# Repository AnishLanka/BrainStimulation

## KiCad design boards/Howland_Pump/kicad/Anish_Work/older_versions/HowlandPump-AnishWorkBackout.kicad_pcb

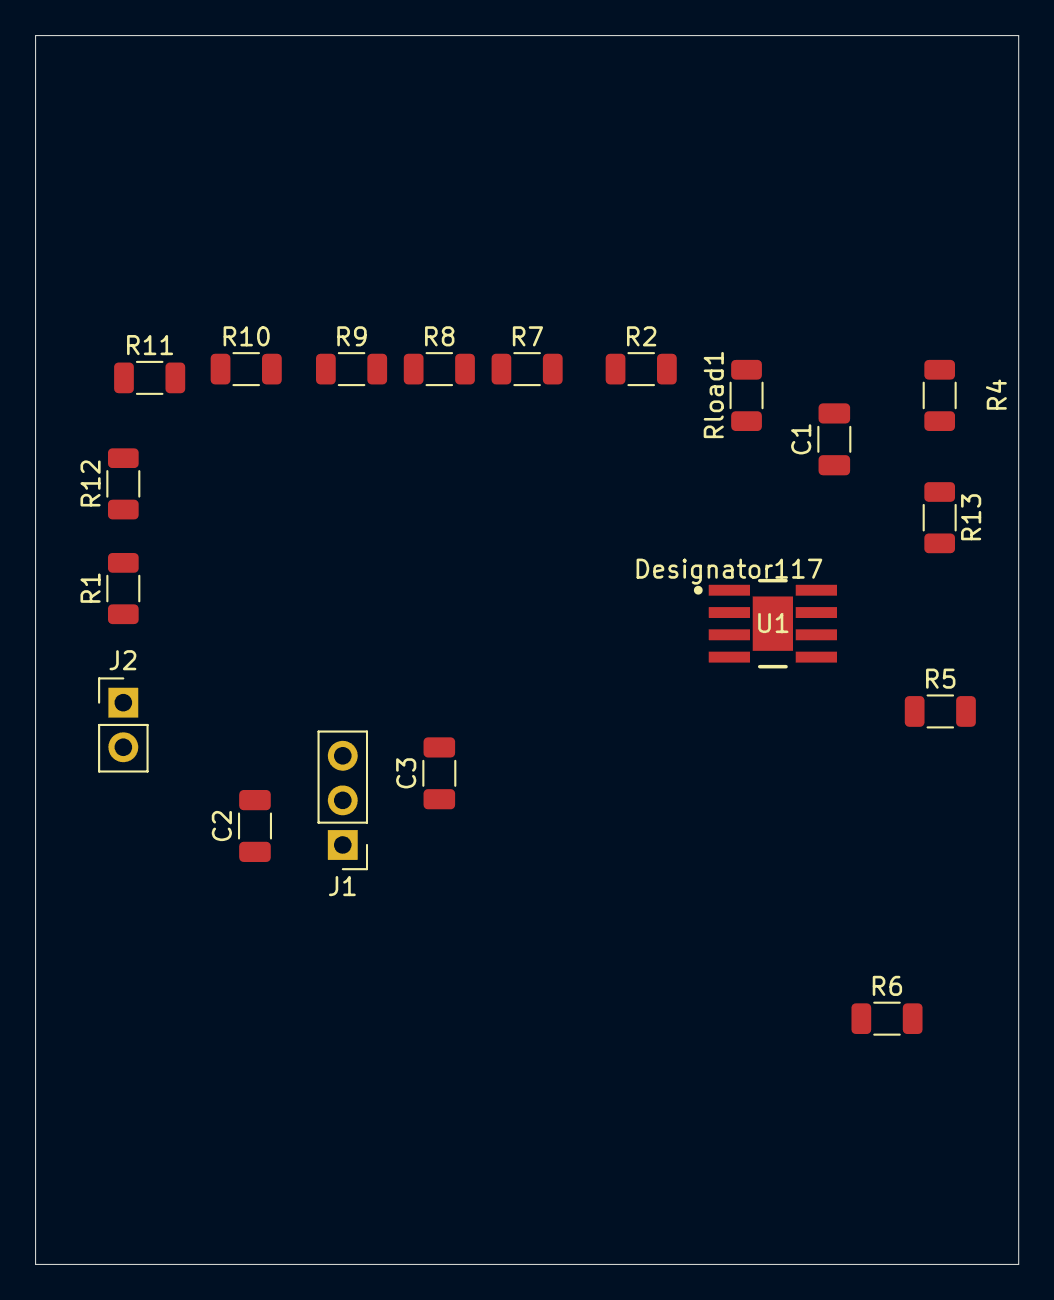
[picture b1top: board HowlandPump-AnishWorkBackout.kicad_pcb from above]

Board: 2 copper layers, 56.0 x 70.0 mm, 19 parts (0 on the bottom side), 16 nets, no tracks yet.

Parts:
C1: 30pF; C_1206_3216Metric
C2, C3: 100nF; C_1206_3216Metric
J1: Conn_01x03; PinHeader_1x03_P2.54mm_Vertical
J2: Conn_01x02; PinHeader_1x02_P2.54mm_Vertical
R1, R5, R6: 100K; R_1206_3216Metric
R2, R7, R8, R9, R10: 9.1K; R_1206_3216Metric
R4: 200; R_1206_3216Metric
R11: 20K; R_1206_3216Metric
R12: 30K; R_1206_3216Metric
R13: 300; R_1206_3216Metric
Rload1: 2K; R_1206_3216Metric
U1: OPA462IDDA; DDA0008J-IPC_A

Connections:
+40: C2.1, J1.1, U1.7 (V+)
-40: C3.2, J1.3, U1.4 (V-), U1.9 (PowerPAD)
GND: C1.2, C2.2, C3.1, J1.2, J2.2, R6.1, Rload1.1, U1.1 (E_D_Com)
unnamed: J2.1, R1.1
unnamed: R2.1, R7.2
unnamed: R2.2, R4.1, Rload1.2
unnamed: R7.1, R8.2
unnamed: R8.1, R9.2
unnamed: R10.1, R11.2
unnamed: R9.1, R10.2
unnamed: R11.1, R12.2
unnamed: R4.2, R13.1
unnamed: R1.2, R12.1, U1.3 (+IN)
unnamed: R5.1, R6.2, U1.2 (-IN)
unnamed: C1.1, U1.8 (E_D)
unnamed: R5.2, R13.2, U1.6 (OUT)

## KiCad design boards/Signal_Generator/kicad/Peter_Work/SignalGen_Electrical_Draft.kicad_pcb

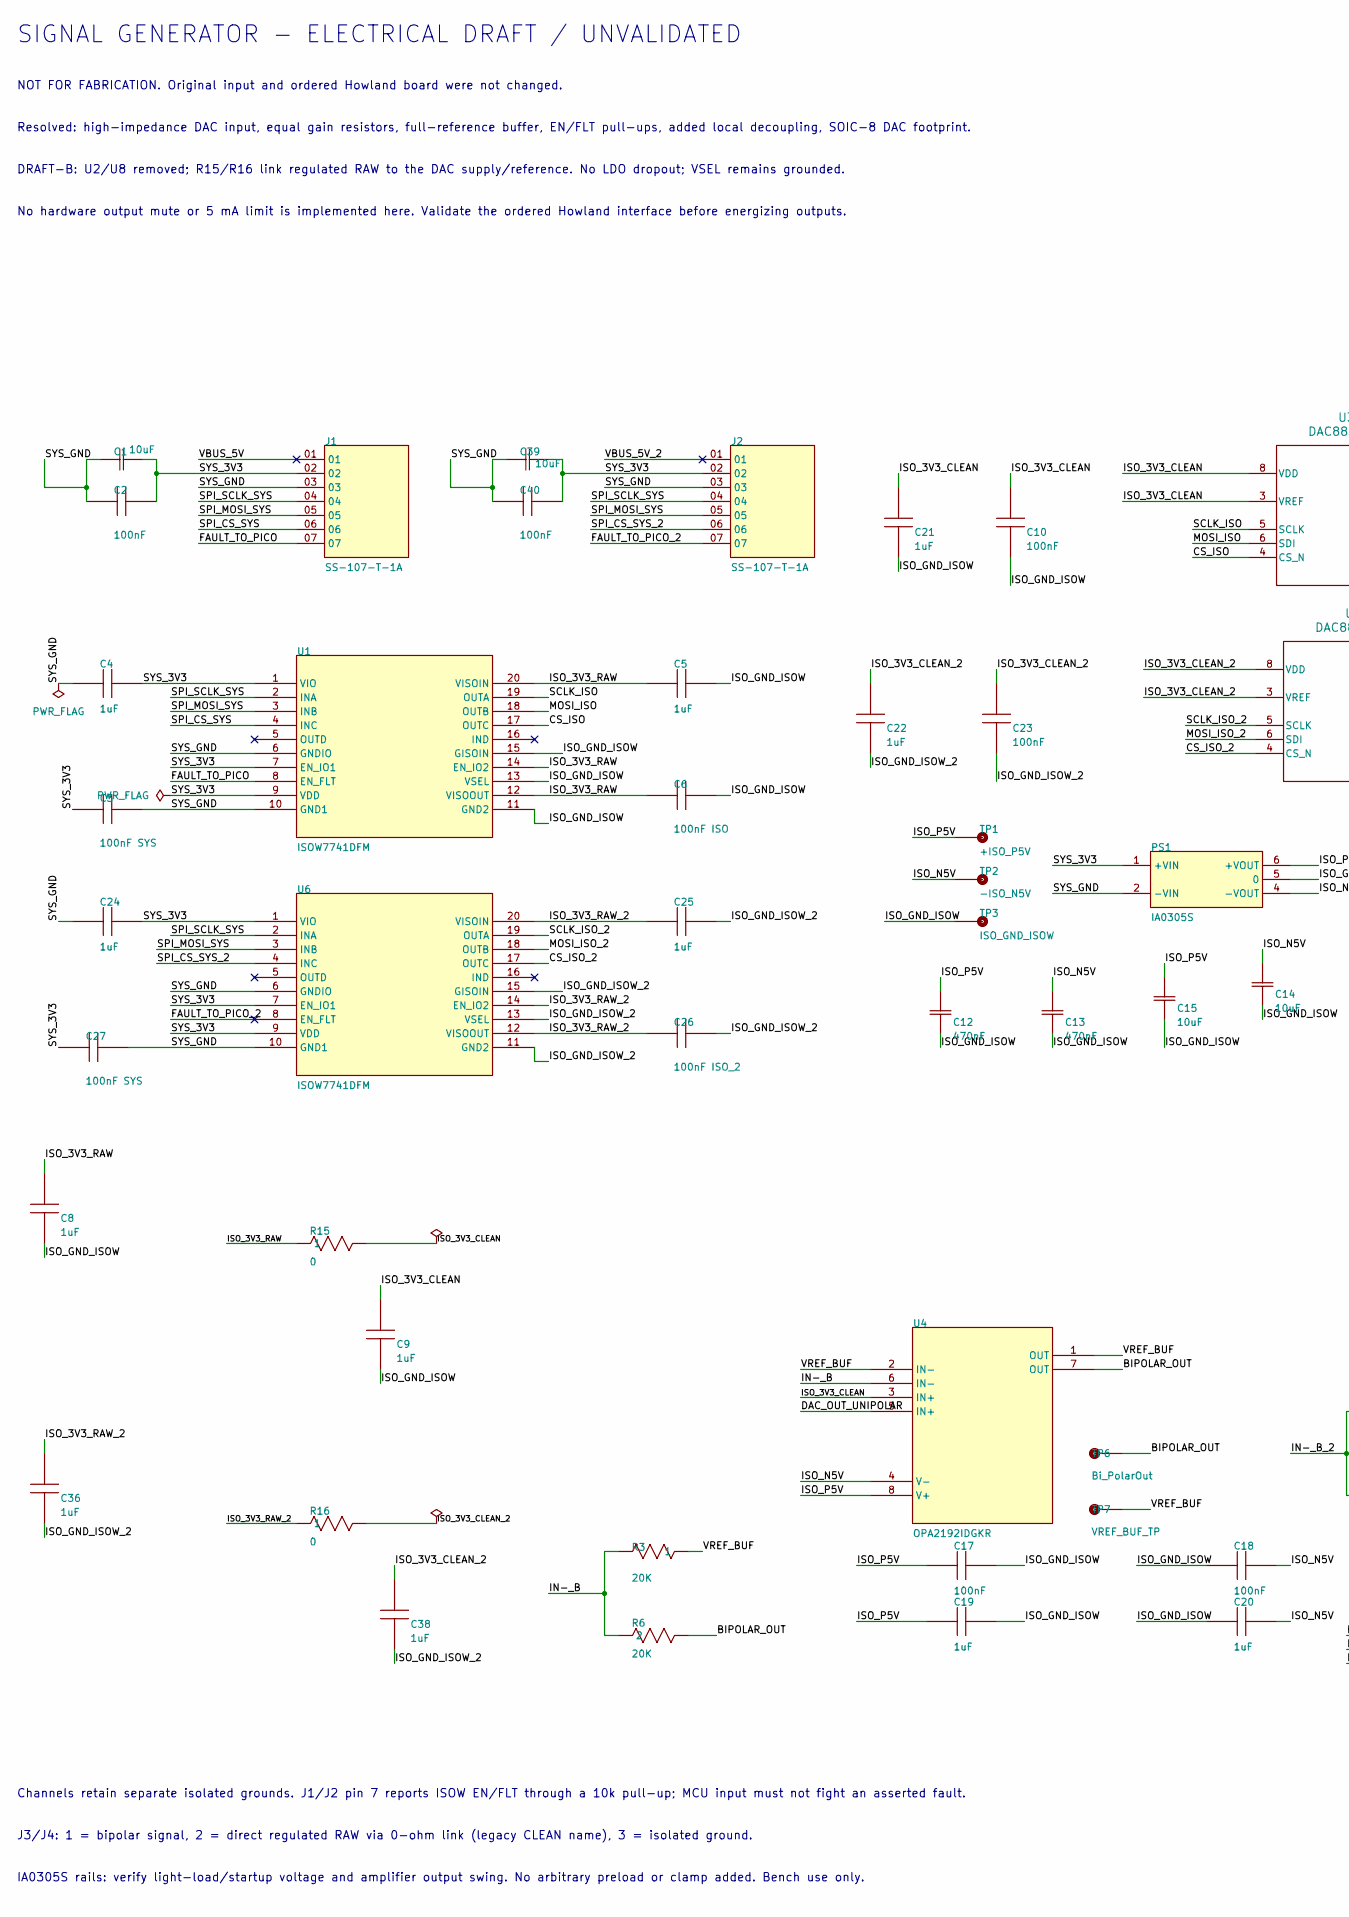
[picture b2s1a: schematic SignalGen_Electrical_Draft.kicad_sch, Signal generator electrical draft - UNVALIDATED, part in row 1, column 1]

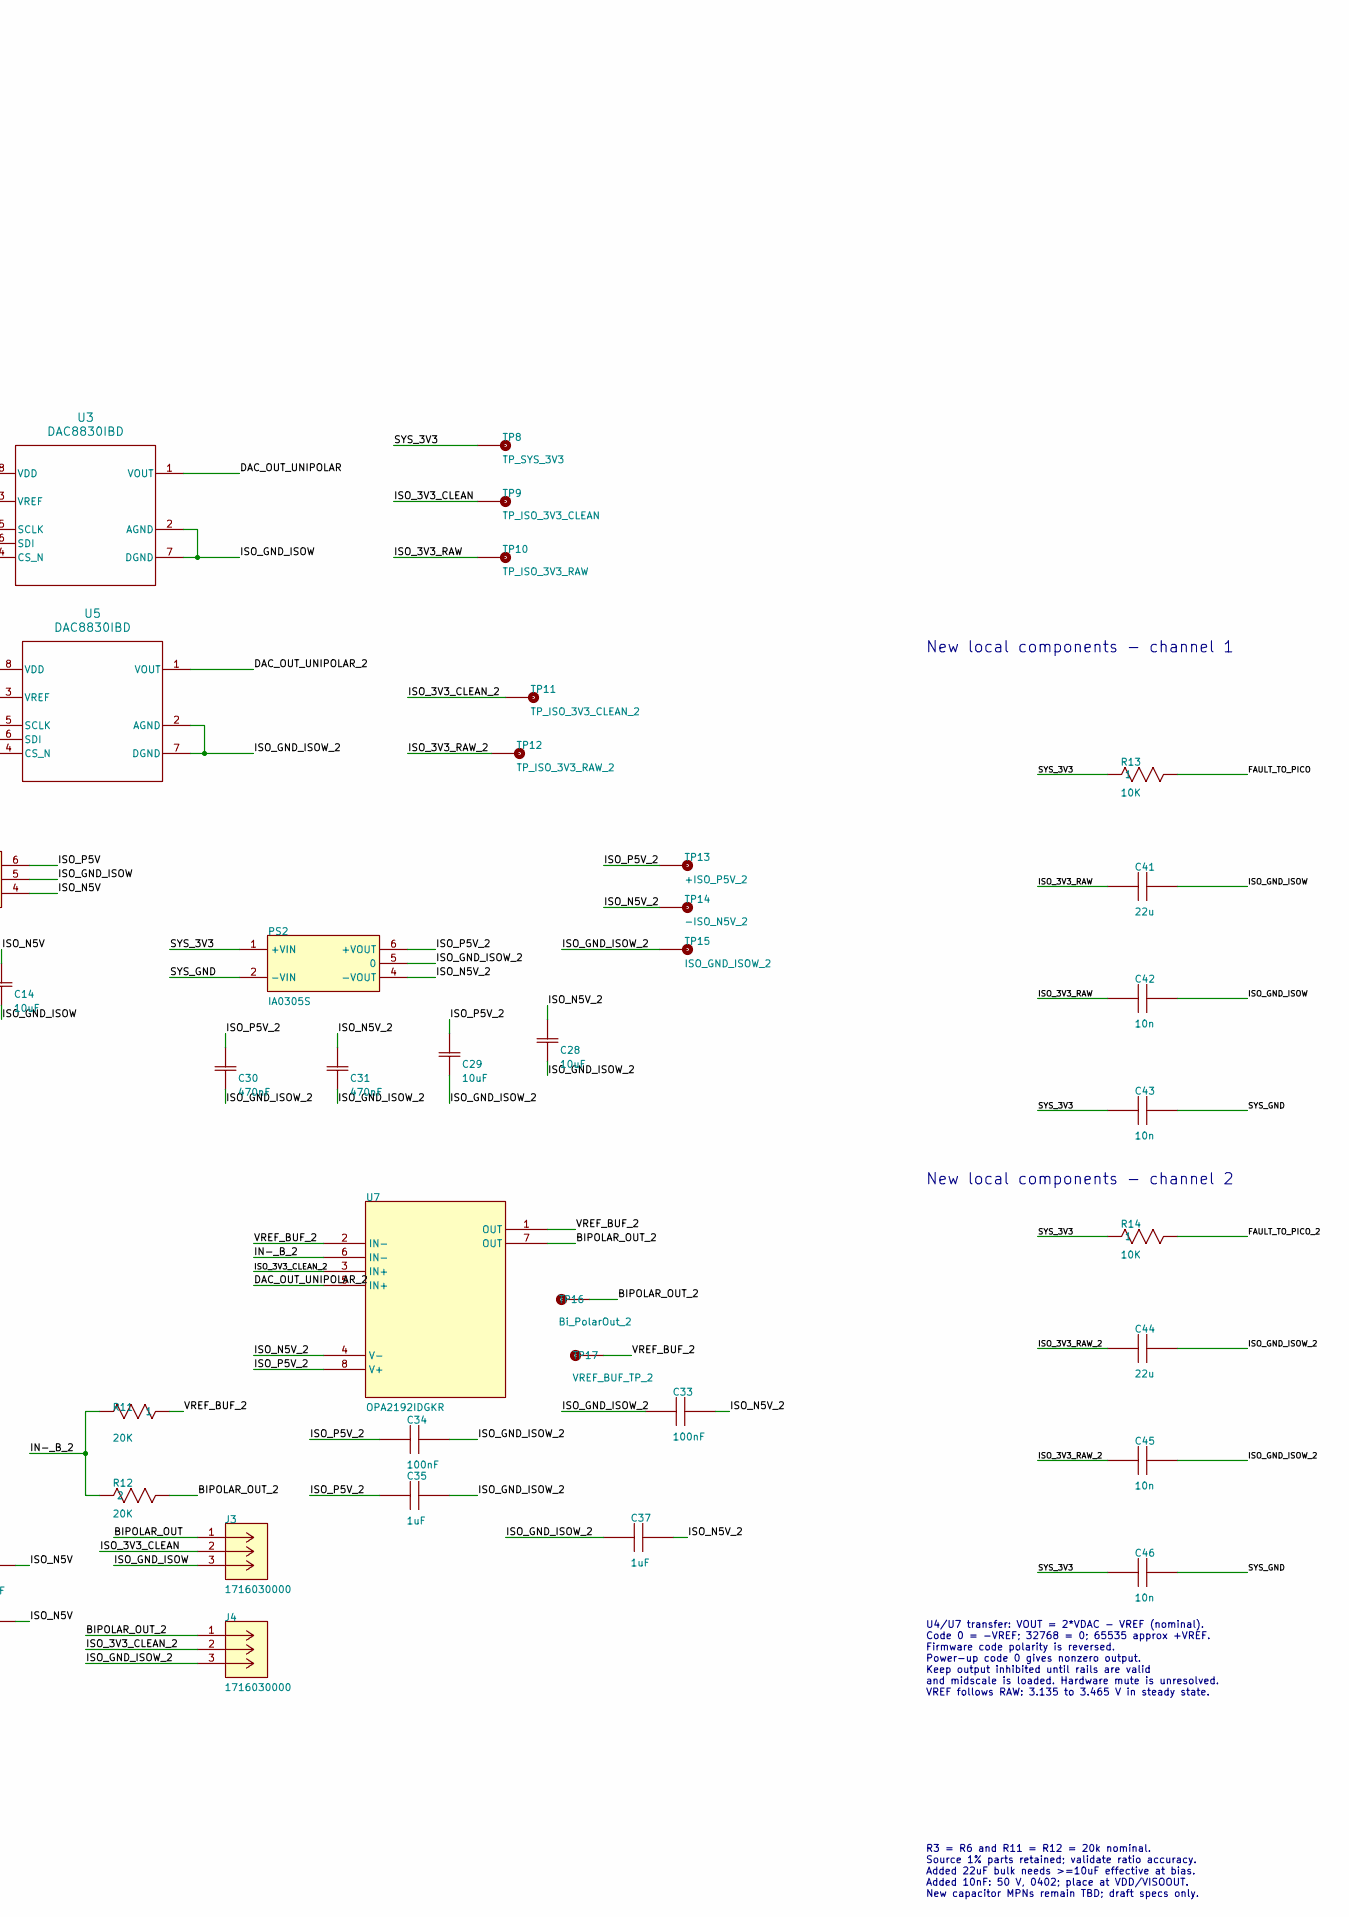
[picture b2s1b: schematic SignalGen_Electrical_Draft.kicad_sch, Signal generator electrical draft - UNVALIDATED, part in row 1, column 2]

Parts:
C1: 10uF; C1_G-21_MUR; MANUFACTURER_PART_NUMBER GRM21BR61E106KA73L
C2: 100nF; C2_CAPC1608X90N; MOUSER PART NUMBER 603-CC603KRX7R8BB104
C3: 100nF SYS; C3_CAPC1608X90N; MOUSER PART NUMBER 603-CC603KRX7R8BB104
C4: 1uF; C4_INDC1608X90N; MOUSER PART NUMBER *
C5: 1uF; C5_INDC1608X90N; MOUSER PART NUMBER *
C6: 100nF ISO; C6_CAPC1608X90N; MOUSER PART NUMBER 603-CC603KRX7R8BB104
C8: 1uF; C8_INDC1608X90N; MOUSER PART NUMBER *
C9: 1uF; C9_INDC1608X90N; MOUSER PART NUMBER *
C10: 100nF; C10_CAPC1608X90N; MOUSER PART NUMBER 603-CC603KRX7R8BB104
C12: 470nF; C12_CAP_1608_TDK; MANUFACTURER_PART_NUMBER C1608X7R1H474K080AC
C13: 470nF; C13_CAP_1608_TDK; MANUFACTURER_PART_NUMBER C1608X7R1H474K080AC
C14: 10uF; C14_G-21_MUR; MANUFACTURER_PART_NUMBER GRM21BR61E106KA73L
C15: 10uF; C15_G-21_MUR; MANUFACTURER_PART_NUMBER GRM21BR61E106KA73L
C17: 100nF; C17_CAPC1608X90N; MOUSER PART NUMBER 603-CC603KRX7R8BB104
C18: 100nF; C18_CAPC1608X90N; MOUSER PART NUMBER 603-CC603KRX7R8BB104
C19: 1uF; C19_INDC1608X90N; MOUSER PART NUMBER *
C20: 1uF; C20_INDC1608X90N; MOUSER PART NUMBER *
C21: 1uF; C21_INDC1608X90N; MOUSER PART NUMBER *
C22: 1uF; C22_INDC1608X90N; MOUSER PART NUMBER *
C23: 100nF; C23_CAPC1608X90N; MOUSER PART NUMBER 603-CC603KRX7R8BB104
C24: 1uF; C24_INDC1608X90N; MOUSER PART NUMBER *
C25: 1uF; C25_INDC1608X90N; MOUSER PART NUMBER *
C26: 100nF ISO_2; C26_CAPC1608X90N; MOUSER PART NUMBER 603-CC603KRX7R8BB104
C27: 100nF SYS; C27_CAPC1608X90N; MOUSER PART NUMBER 603-CC603KRX7R8BB104
C28: 10uF; C28_G-21_MUR; MANUFACTURER_PART_NUMBER GRM21BR61E106KA73L
C29: 10uF; C29_G-21_MUR; MANUFACTURER_PART_NUMBER GRM21BR61E106KA73L
C30: 470nF; C30_CAP_1608_TDK; MANUFACTURER_PART_NUMBER C1608X7R1H474K080AC
C31: 470nF; C31_CAP_1608_TDK; MANUFACTURER_PART_NUMBER C1608X7R1H474K080AC
C33: 100nF; C33_CAPC1608X90N; MOUSER PART NUMBER 603-CC603KRX7R8BB104
C34: 100nF; C34_CAPC1608X90N; MOUSER PART NUMBER 603-CC603KRX7R8BB104
C35: 1uF; C35_INDC1608X90N; MOUSER PART NUMBER *
C36: 1uF; C36_INDC1608X90N; MOUSER PART NUMBER *
C37: 1uF; C37_INDC1608X90N; MOUSER PART NUMBER *
C38: 1uF; C38_INDC1608X90N; MOUSER PART NUMBER *
C39: 10uF; C39_G-21_MUR; MANUFACTURER_PART_NUMBER GRM21BR61E106KA73L
C40: 100nF; C40_CAPC1608X90N; MOUSER PART NUMBER 603-CC603KRX7R8BB104
C41, C44: 22u; C_1206_3216Metric; Voltage 16V; MOUSER PART NUMBER *
C42, C43, C45, C46: 10n; C_0402_1005Metric; Voltage 50V; MOUSER PART NUMBER *
J1: SS-107-T-1A; J1_SAMTEC_SS-107-T-1A
J2: SS-107-T-1A; J2_SAMTEC_SS-107-T-1A
J3: 1716030000; J3_CONN_LM_5.080390_WED; MANUFACTURER_PART_NUMBER 1716030000
J4: 1716030000; J4_CONN_LM_5.080390_WED; MANUFACTURER_PART_NUMBER 1716030000
PS1: IA0305S; PS1_XP_IA0305S
PS2: IA0305S; PS2_XP_IA0305S
R3: 20K; R3_RC0603N_YAG; MANUFACTURER_PART_NUMBER RC0603FR-0720KL
R6: 20K; R6_RC0603N_YAG; MANUFACTURER_PART_NUMBER RC0603FR-0720KL
R11: 20K; R11_RC0603N_YAG; MANUFACTURER_PART_NUMBER RC0603FR-0720KL
R12: 20K; R12_RC0603N_YAG; MANUFACTURER_PART_NUMBER RC0603FR-0720KL
R13, R14: 10K; R_0603_1608Metric; MANUFACTURER_PART_NUMBER RC0603FR-0710KL
R15, R16: 0; R_0603_1608Metric; Tolerance Jumper; MANUFACTURER_PART_NUMBER TBD - standard 0603 zero-ohm jumper
TP1: +ISO_P5V; TP1_KEYSTONE_5016
TP2: -ISO_N5V; TP2_KEYSTONE_5016
TP3: ISO_GND_ISOW; TP3_KEYSTONE_5016
TP6: Bi_PolarOut; TP6_KEYSTONE_5016
TP7: VREF_BUF_TP; TP7_KEYSTONE_5016
TP8: TP_SYS_3V3; TP8_KEYSTONE_5016
TP9: TP_ISO_3V3_CLEAN; TP9_KEYSTONE_5016
TP10: TP_ISO_3V3_RAW; TP10_KEYSTONE_5016
TP11: TP_ISO_3V3_CLEAN_2; TP11_KEYSTONE_5016
TP12: TP_ISO_3V3_RAW_2; TP12_KEYSTONE_5016
TP13: +ISO_P5V_2; TP13_KEYSTONE_5016
TP14: -ISO_N5V_2; TP14_KEYSTONE_5016
TP15: ISO_GND_ISOW_2; TP15_KEYSTONE_5016
TP16: Bi_PolarOut_2; TP16_KEYSTONE_5016
TP17: VREF_BUF_TP_2; TP17_KEYSTONE_5016
U1: ISOW7741DFM; U1_SOIC20_DFM_TEX; MANUFACTURER_PART_NUMBER ISOW7741DFM
U3, U5: DAC8830IBD; SOIC-8_3.9x4.9mm_P1.27mm
U4: OPA2192IDGKR; U4_DGK0008A_N_TEX; MANUFACTURER_PART_NUMBER OPA2192IDGKR
U6: ISOW7741DFM; U6_SOIC20_DFM_TEX; MANUFACTURER_PART_NUMBER ISOW7741DFM
U7: OPA2192IDGKR; U7_DGK0008A_N_TEX; MANUFACTURER_PART_NUMBER OPA2192IDGKR

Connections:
/BIPOLAR_OUT: J3.1, R6.1, TP6.TP (TP_TP), U4.7 (OUT)
/BIPOLAR_OUT_2: J4.1, R12.1, TP16.TP (TP_TP), U7.7 (OUT)
/CS_ISO: U1.17 (OUTC), U3.4 (CS_N)
/CS_ISO_2: U5.4 (CS_N), U6.17 (OUTC)
/DAC_OUT_UNIPOLAR: U3.1 (VOUT), U4.5 (IN+)
/DAC_OUT_UNIPOLAR_2: U5.1 (VOUT), U7.5 (IN+)
/FAULT_TO_PICO: J1.07, R13.2, U1.8 (EN_FLT)
/FAULT_TO_PICO_2: J2.07, R14.2, U6.8 (EN_FLT)
/IN-_B: R3.2, R6.2, U4.6 (IN-)
/IN-_B_2: R11.2, R12.2, U7.6 (IN-)
/ISO_3V3_CLEAN: C9.2, C10.2, C21.2, J3.2, R15.2, TP9.TP (TP_TP), U3.3 (VREF), U3.8 (VDD), U4.3 (IN+)
/ISO_3V3_CLEAN_2: C22.2, C23.2, C38.2, J4.2, R16.2, TP11.TP (TP_TP), U5.3 (VREF), U5.8 (VDD), U7.3 (IN+)
/ISO_3V3_RAW: C5.1, C6.2, C8.2, C41.1, C42.1, R15.1, TP10.TP (TP_TP), U1.12 (VISOOUT), U1.14 (EN_IO2), U1.20 (VISOIN)
/ISO_3V3_RAW_2: C25.1, C26.2, C36.2, C44.1, C45.1, R16.1, TP12.TP (TP_TP), U6.12 (VISOOUT), U6.14 (EN_IO2), U6.20 (VISOIN)
/ISO_GND_ISOW: C5.2, C6.1, C8.1, C9.1, C10.1, C12.1, C13.1, C14.1, C15.1, C17.2, C18.1, C19.2, C20.1, C21.1, C41.2, C42.2, J3.3, PS1.5 (0), TP3.TP (TP_TP), U1.11 (GND2), U1.13 (VSEL), U1.15 (GISOIN), U3.2 (AGND), U3.7 (DGND)
/ISO_GND_ISOW_2: C22.1, C23.1, C25.2, C26.1, C28.1, C29.1, C30.1, C31.1, C33.1, C34.2, C35.2, C36.1, C37.1, C38.1, C44.2, C45.2, J4.3, PS2.5 (0), TP15.TP (TP_TP), U5.2 (AGND), U5.7 (DGND), U6.11 (GND2), U6.13 (VSEL), U6.15 (GISOIN)
/ISO_N5V: C13.2, C14.2, C18.2, C20.2, PS1.4 (-VOUT), TP2.TP (TP_TP), U4.4 (V-)
/ISO_N5V_2: C28.2, C31.2, C33.2, C37.2, PS2.4 (-VOUT), TP14.TP (TP_TP), U7.4 (V-)
/ISO_P5V: C12.2, C15.2, C17.1, C19.1, PS1.6 (+VOUT), TP1.TP (TP_TP), U4.8 (V+)
/ISO_P5V_2: C29.2, C30.2, C34.1, C35.1, PS2.6 (+VOUT), TP13.TP (TP_TP), U7.8 (V+)
/MOSI_ISO: U1.18 (OUTB), U3.6 (SDI)
/MOSI_ISO_2: U5.6 (SDI), U6.18 (OUTB)
/SCLK_ISO: U1.19 (OUTA), U3.5 (SCLK)
/SCLK_ISO_2: U5.5 (SCLK), U6.19 (OUTA)
/SPI_CS_SYS: J1.06, U1.4 (INC)
/SPI_CS_SYS_2: J2.06, U6.4 (INC)
/SPI_MOSI_SYS: J1.05, J2.05, U1.3 (INB), U6.3 (INB)
/SPI_SCLK_SYS: J1.04, J2.04, U1.2 (INA), U6.2 (INA)
/SYS_3V3: C1.1, C2.1, C3.2, C4.2, C24.2, C27.2, C39.1, C40.1, C43.1, C46.1, J1.02, J2.02, PS1.1 (+VIN), PS2.1 (+VIN), R13.1, R14.1, TP8.TP (TP_TP), U1.1 (VIO), U1.7 (EN_IO1), U1.9 (VDD), U6.1 (VIO), U6.7 (EN_IO1), U6.9 (VDD)
/SYS_GND: C1.2, C2.2, C3.1, C4.1, C24.1, C27.1, C39.2, C40.2, C43.2, C46.2, J1.03, J2.03, PS1.2 (-VIN), PS2.2 (-VIN), U1.6 (GNDIO), U1.10 (GND1), U6.6 (GNDIO), U6.10 (GND1)
/VBUS_5V: J1.01
/VBUS_5V_2: J2.01
/VREF_BUF: R3.1, TP7.TP (TP_TP), U4.1 (OUT), U4.2 (IN-)
/VREF_BUF_2: R11.1, TP17.TP (TP_TP), U7.1 (OUT), U7.2 (IN-)

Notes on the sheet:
SIGNAL GENERATOR - ELECTRICAL DRAFT / UNVALIDATED
NOT FOR FABRICATION. Original input and ordered Howland board were not changed.
Resolved: high-impedance DAC input, equal gain resistors, full-reference buffer, EN/FLT pull-ups, added local decoupling, SOIC-8 DAC footprint.
DRAFT-B: U2/U8 removed; R15/R16 link regulated RAW to the DAC supply/reference. No LDO dropout; VSEL remains grounded.
No hardware output mute or 5 mA limit is implemented here. Validate the ordered Howland interface before energizing outputs.
New local components - channel 1
New local components - channel 2
U4/U7 transfer: VOUT = 2*VDAC - VREF (nominal). Code 0 = -VREF; 32768 = 0; 65535 approx +VREF. Firmware code polarity is reversed. Power-up code 0 gives nonzero output. Keep output inhibited until rails are valid and midscale is loaded. Hardware mute is unresolved. VREF follows RAW: 3.135 to 3.465 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
R3 = R6 and R11 = R12 = 20k nominal. Source 1% parts retained; validate ratio accuracy. Added 22uF bulk needs >=10uF effective at bias. Added 10nF: 50 V, 0402; place at VDD/VISOOUT. New capacitor MPNs remain TBD; draft specs only.
Channels retain separate isolated grounds. J1/J2 pin 7 reports ISOW EN/FLT through a 10k pull-up; MCU input must not fight an asserted fault.
J3/J4: 1 = bipolar signal, 2 = direct regulated RAW via 0-ohm link (legacy CLEAN name), 3 = isolated ground.
IA0305S rails: verify light-load/startup voltage and amplifier output swing. No arbitrary preload or clamp added. Bench use only.

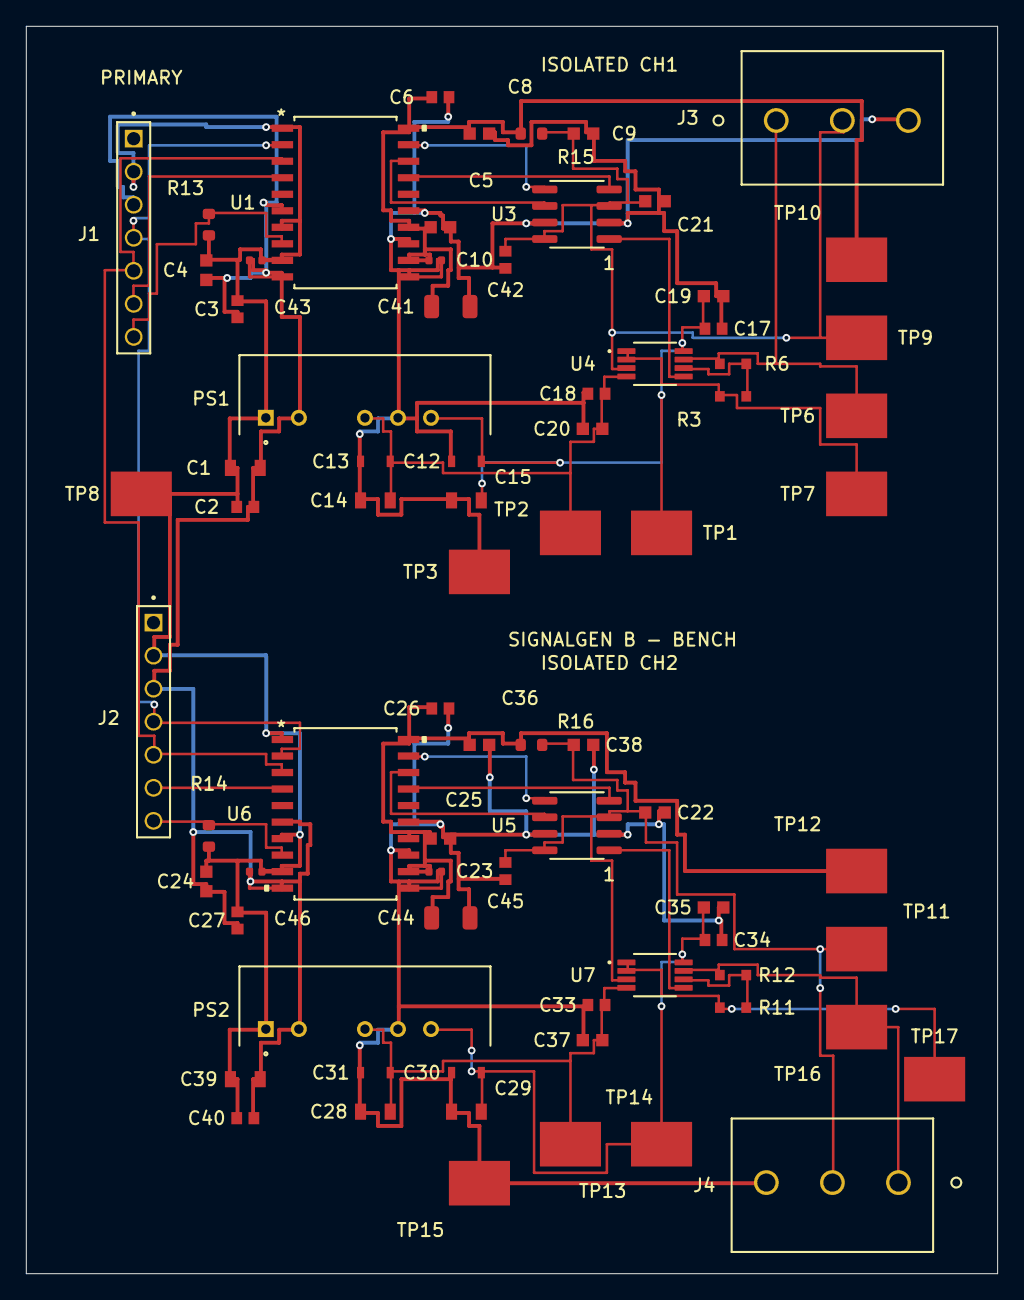
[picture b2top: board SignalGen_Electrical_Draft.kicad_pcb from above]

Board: 2 copper layers, 74.7 x 95.9 mm, 77 parts (0 on the bottom side), 32 nets.

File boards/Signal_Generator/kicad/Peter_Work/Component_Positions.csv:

Ref,Val,Package,PosX,PosY,Rot,Side
"C1","10uF","C1_G-21_MUR",16.836900,61.954600,0.000000,top
"C2","100nF","C2_CAPC1608X90N",16.836900,58.954600,0.000000,top
"C3","100nF SYS","C3_CAPC1608X90N",16.236900,74.154600,90.000000,top
"C4","1uF","C4_INDC1608X90N",13.836900,77.154600,90.000000,top
"C5","1uF","C5_INDC1608X90N",31.836900,80.454600,0.000000,top
"C6","100nF ISO","C6_CAPC1608X90N",31.836900,90.454600,180.000000,top
"C8","1uF","C8_INDC1608X90N",34.836900,87.654600,180.000000,top
"C9","1uF","C9_INDC1608X90N",42.836900,87.654600,180.000000,top
"C10","100nF","C10_CAPC1608X90N",36.836900,77.954600,90.000000,top
"C12","470nF","C12_CAP_1608_TDK",33.836900,62.454600,0.000000,top
"C13","470nF","C13_CAP_1608_TDK",26.836900,62.454600,0.000000,top
"C14","10uF","C14_G-21_MUR",26.836900,59.454600,0.000000,top
"C15","10uF","C15_G-21_MUR",33.836900,59.454600,0.000000,top
"C17","100nF","C17_CAPC1608X90N",52.836900,72.654600,0.000000,top
"C18","100nF","C18_CAPC1608X90N",43.836900,67.654600,0.000000,top
"C19","1uF","C19_INDC1608X90N",52.836900,75.154600,0.000000,top
"C20","1uF","C20_INDC1608X90N",43.536900,64.954600,0.000000,top
"C21","1uF","C21_INDC1608X90N",48.336900,82.454600,180.000000,top
"C22","1uF","C22_INDC1608X90N",48.336900,35.454600,180.000000,top
"C23","100nF","C23_CAPC1608X90N",36.836900,30.954600,90.000000,top
"C24","1uF","C24_INDC1608X90N",13.836900,30.154600,90.000000,top
"C25","1uF","C25_INDC1608X90N",31.836900,33.454600,0.000000,top
"C26","100nF ISO_2","C26_CAPC1608X90N",31.836900,43.454600,180.000000,top
"C27","100nF SYS","C27_CAPC1608X90N",16.236900,27.154600,90.000000,top
"C28","10uF","C28_G-21_MUR",26.836900,12.454600,0.000000,top
"C29","10uF","C29_G-21_MUR",33.836900,12.454600,0.000000,top
"C30","470nF","C30_CAP_1608_TDK",33.836900,15.454600,0.000000,top
"C31","470nF","C31_CAP_1608_TDK",26.836900,15.454600,0.000000,top
"C33","100nF","C33_CAPC1608X90N",43.836900,20.654600,0.000000,top
"C34","100nF","C34_CAPC1608X90N",52.836900,25.654600,0.000000,top
"C35","1uF","C35_INDC1608X90N",52.836900,28.154600,0.000000,top
"C36","1uF","C36_INDC1608X90N",34.836900,40.654600,180.000000,top
"C37","1uF","C37_INDC1608X90N",43.536900,17.954600,0.000000,top
"C38","1uF","C38_INDC1608X90N",42.836900,40.654600,180.000000,top
"C39","10uF","C39_G-21_MUR",16.836900,14.954600,0.000000,top
"C40","100nF","C40_CAPC1608X90N",16.836900,11.954600,0.000000,top
"C41","22u","C_1206_3216Metric",32.636900,74.354600,0.000000,top
"C42","10n","C_0402_1005Metric",31.436900,77.909600,0.000000,top
"C43","10n","C_0402_1005Metric",17.636900,77.909600,180.000000,top
"C44","22u","C_1206_3216Metric",32.636900,27.354600,0.000000,top
"C45","10n","C_0402_1005Metric",31.436900,30.909600,0.000000,top
"C46","10n","C_0402_1005Metric",17.636900,30.909600,180.000000,top
"J1","SS-107-T-1A","J1_SAMTEC_SS-107-T-1A",8.255000,87.266001,90.000000,top
"J2","SS-107-T-1A","J2_SAMTEC_SS-107-T-1A",9.779000,50.055000,90.000000,top
"J3","1716030000","J3_CONN_LM_5.080390_WED",57.658000,88.663000,0.000000,top
"J4","1716030000","J4_CONN_LM_5.080390_WED",67.056000,7.002000,180.000000,top
"PS1","IA0305S","PS1_XP_IA0305S",18.415000,65.803000,0.000000,top
"PS2","IA0305S","PS2_XP_IA0305S",18.415000,18.803000,0.000000,top
"R3","20K","R3_RC0603N_YAG",54.336900,67.454600,0.000000,top
"R6","20K","R6_RC0603N_YAG",54.336900,69.954600,0.000000,top
"R11","20K","R11_RC0603N_YAG",54.336900,20.454600,0.000000,top
"R12","20K","R12_RC0603N_YAG",54.336900,22.954600,0.000000,top
"R13","10K","R_0603_1608Metric",14.036900,80.654600,90.000000,top
"R14","10K","R_0603_1608Metric",14.036900,33.654600,90.000000,top
"R15","0","R_0603_1608Metric",38.836900,87.654600,0.000000,top
"R16","0","R_0603_1608Metric",38.836900,40.654600,0.000000,top
"TP1","+ISO_P5V","TP1_KEYSTONE_5016",48.836900,56.954600,0.000000,top
"TP2","-ISO_N5V","TP2_KEYSTONE_5016",41.836900,56.954600,0.000000,top
"TP3","ISO_GND_ISOW","TP3_KEYSTONE_5016",34.836900,53.954600,0.000000,top
"TP6","Bi_PolarOut","TP6_KEYSTONE_5016",63.836900,65.954600,0.000000,top
"TP7","VREF_BUF_TP","TP7_KEYSTONE_5016",63.836900,59.954600,0.000000,top
"TP8","TP_SYS_3V3","TP8_KEYSTONE_5016",8.836900,59.954600,0.000000,top
"TP9","TP_ISO_3V3_CLEAN","TP9_KEYSTONE_5016",63.836900,71.954600,0.000000,top
"TP10","TP_ISO_3V3_RAW","TP10_KEYSTONE_5016",63.836900,77.954600,0.000000,top
"TP11","TP_ISO_3V3_CLEAN_2","TP11_KEYSTONE_5016",63.836900,24.954600,0.000000,top
"TP12","TP_ISO_3V3_RAW_2","TP12_KEYSTONE_5016",63.836900,30.954600,0.000000,top
"TP13","+ISO_P5V_2","TP13_KEYSTONE_5016",48.836900,9.954600,0.000000,top
"TP14","-ISO_N5V_2","TP14_KEYSTONE_5016",41.836900,9.954600,0.000000,top
"TP15","ISO_GND_ISOW_2","TP15_KEYSTONE_5016",34.836900,6.954600,0.000000,top
"TP16","Bi_PolarOut_2","TP16_KEYSTONE_5016",63.836900,18.954600,0.000000,top
"TP17","VREF_BUF_TP_2","TP17_KEYSTONE_5016",69.836900,14.954600,0.000000,top
"U1","ISOW7741DFM","U1_SOIC20_DFM_TEX",24.536900,82.354600,0.000000,top
"U3","DAC8830IBD","SOIC-8_3.9x4.9mm_P1.27mm",42.336900,81.454600,180.000000,top
"U4","OPA2192IDGKR","U4_DGK0008A_N_TEX",48.336900,69.954600,0.000000,top
"U5","DAC8830IBD","SOIC-8_3.9x4.9mm_P1.27mm",42.336900,34.454600,180.000000,top
"U6","ISOW7741DFM","U6_SOIC20_DFM_TEX",24.536900,35.354600,0.000000,top
"U7","OPA2192IDGKR","U7_DGK0008A_N_TEX",48.336900,22.954600,0.000000,top

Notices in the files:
parts and their libraries:
COPYRIGHT: Copyright (C) 2025 Ultra Librarian. All rights reserved.
COPYRIGHT: Copyright (C) 2026 Ultra Librarian. All rights reserved.
